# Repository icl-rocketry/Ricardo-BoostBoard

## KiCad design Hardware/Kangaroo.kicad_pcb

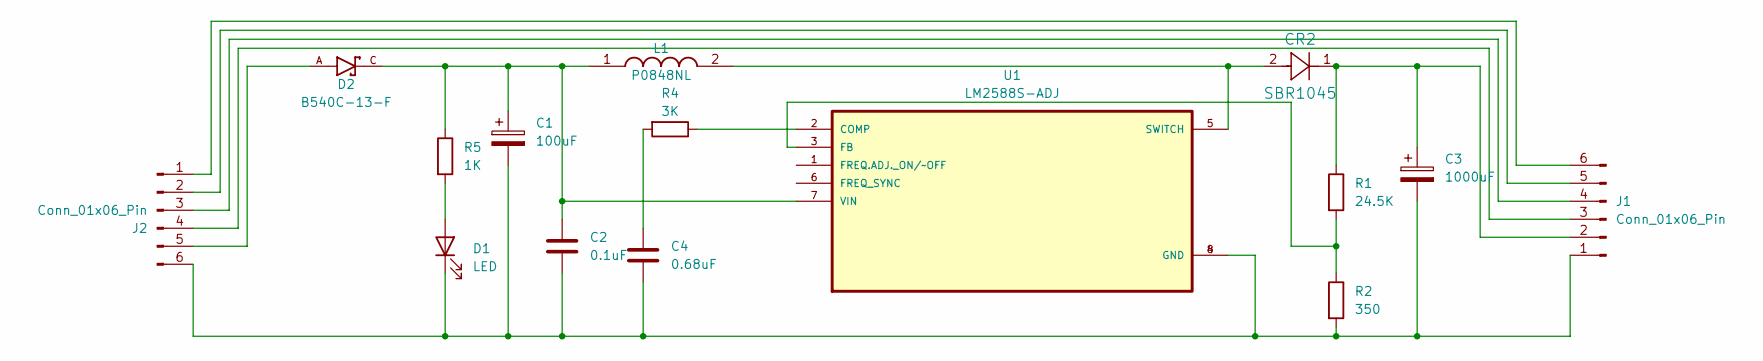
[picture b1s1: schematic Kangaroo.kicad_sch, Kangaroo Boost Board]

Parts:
C1: 100uF; C_0201_0603Metric
C2: 0.1uF; C_0402_1005Metric
C3: 1000uF; C_0201_0603Metric
C4: 0.68uF; R_0805_2012Metric
CR2: SBR1045; DPAK228P990X239-4N
D1: LED; LED_0402_1005Metric
D2: B540C-13-F; DIOM6959X245N; PARTREV V1.0
J1, J2: Conn_01x06_Pin; Molex_Mini-Fit_Jr_5569-06A2_2x03_P4.20mm_Horizontal_No_Moun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
L1: P0848NL; Mouser Part Number 673-P0848NL
R1: 24.5K; R_0402_1005Metric
R2: 350; R_0402_1005Metric
R4: 3K; R_0402_1005Metric
R5: 1K; R_0402_1005Metric
U1: LM2588S-ADJ; TO127P1435X464-8N

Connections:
unnamed: C4.1, R4.2
unnamed: D1.2 (A), R5.2
unnamed: C1.2, C2.2, C3.2, C4.2, D1.1 (K), J1.1, J2.6, R2.2, U1.4 (GND), U1.8 (GND)
unnamed: C3.1, CR2.1, J1.2, R1.1
unnamed: J1.3, J2.4
unnamed: J1.4, J2.3
unnamed: J1.5, J2.2
unnamed: J1.6, J2.1
unnamed: D2.A, J2.5
unnamed: R4.1, U1.2 (COMP)
unnamed: R1.2, R2.1, U1.3 (FB)
unnamed: CR2.2, L1.2, U1.5 (SWITCH)
unnamed: C1.1, C2.1, D2.C, L1.1, R5.1, U1.7 (VIN)

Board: 2 copper layers, 15 parts (0 on the bottom side), 13 nets, no tracks yet.

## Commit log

2024-02-20 Added initial Schematic
2024-02-20 Completed Initial Schematic
    LM2588-ADJ IC with 6 pin socket
2024-02-20 Deleted Unnecessary Files
    ^^
2024-02-20 6 Pin Socket Change
    Schematic Finished - in theory
2024-02-26 Test PCB Design
    Tested PCB design of Kangaroo - proper footprints need to be verified with Shiven.
2024-03-05 Changed Schematic & Footprints Symbols Added
    New correct footprints added
2024-03-06 Specific components added
    Inductor 50uH 5A slim, Diodes (Rectifying and SBR1045)
2024-03-06 Changed Positions of Symbols
